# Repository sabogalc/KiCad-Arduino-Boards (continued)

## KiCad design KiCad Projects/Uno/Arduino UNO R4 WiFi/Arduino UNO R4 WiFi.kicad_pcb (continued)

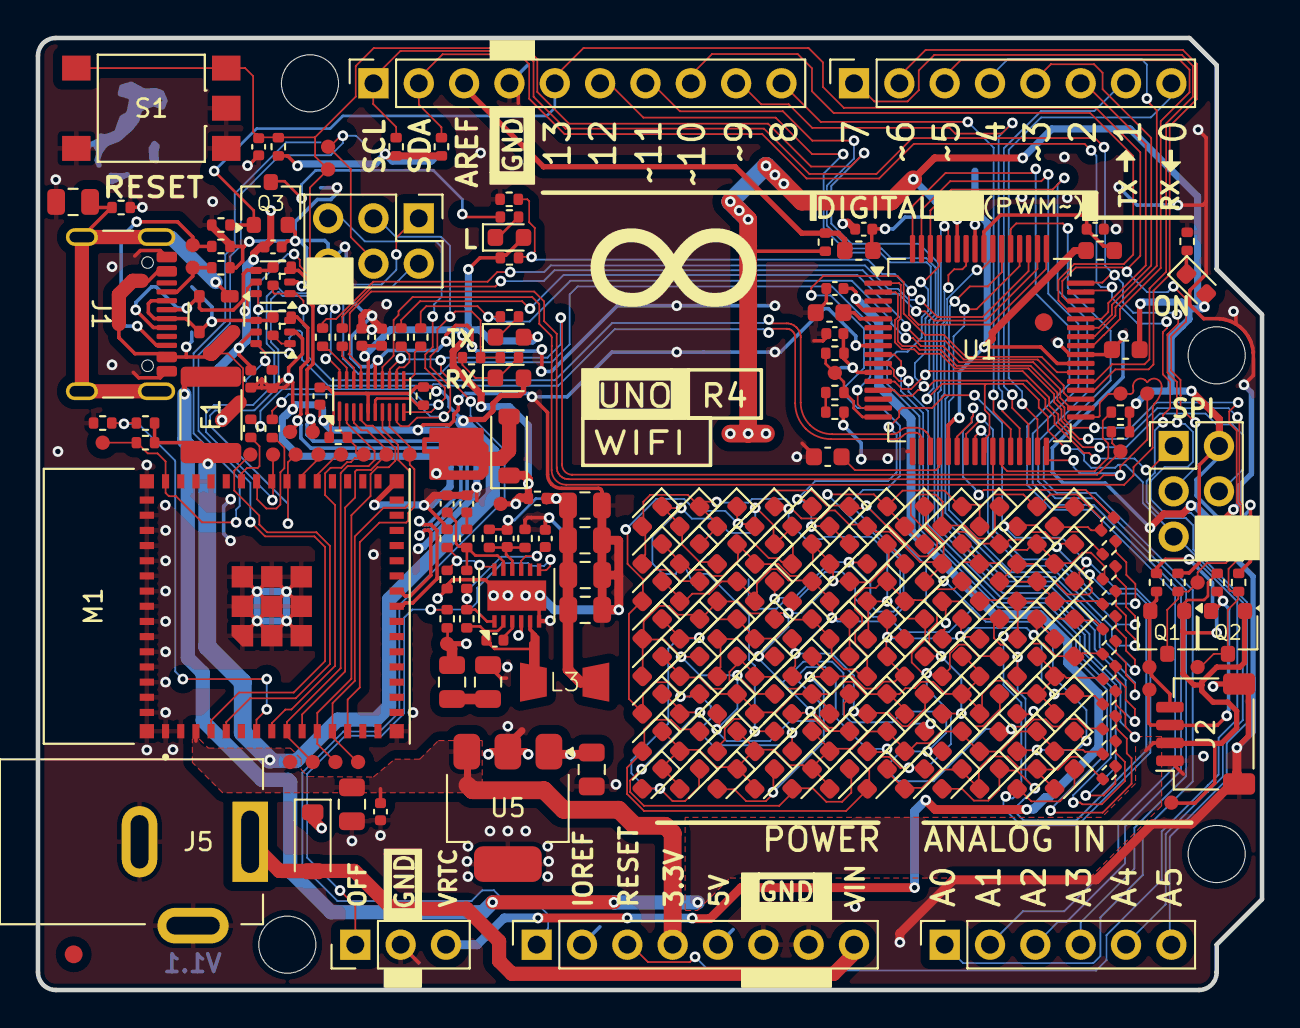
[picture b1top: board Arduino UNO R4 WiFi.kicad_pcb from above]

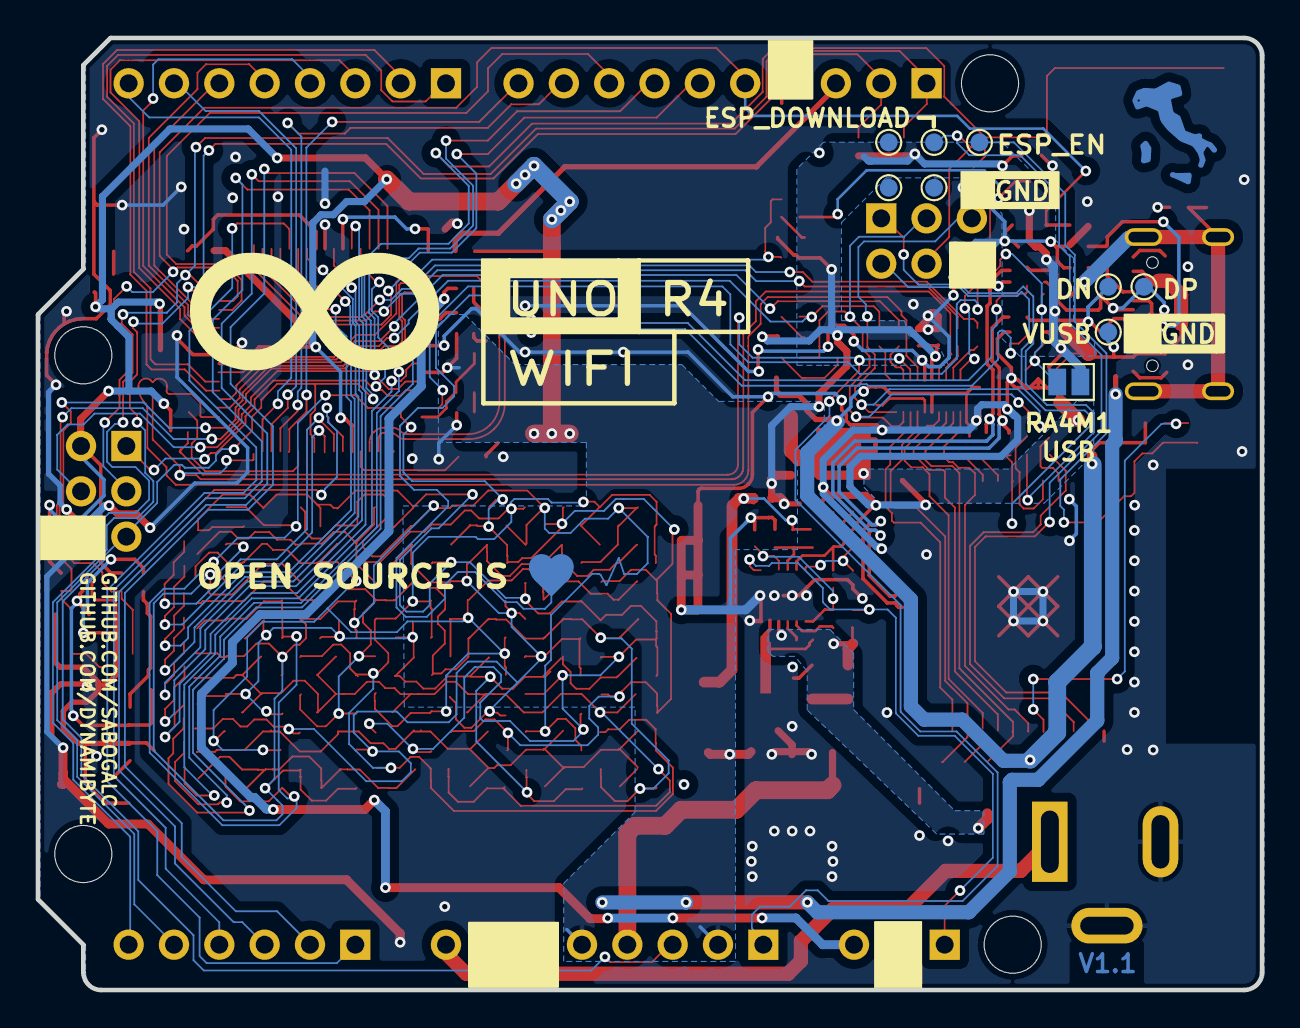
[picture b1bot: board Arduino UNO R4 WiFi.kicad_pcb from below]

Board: 2 copper layers, 68.6 x 53.3 mm, 262 parts (12 on the bottom side), 121 nets.

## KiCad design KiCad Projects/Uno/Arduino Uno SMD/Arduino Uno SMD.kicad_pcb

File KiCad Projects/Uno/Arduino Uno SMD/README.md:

# UNO R3 SMD
This board and its design process are essentially the same as the regular R3.

Below are the screenshots of this board from KiCad's 3D board viewer.

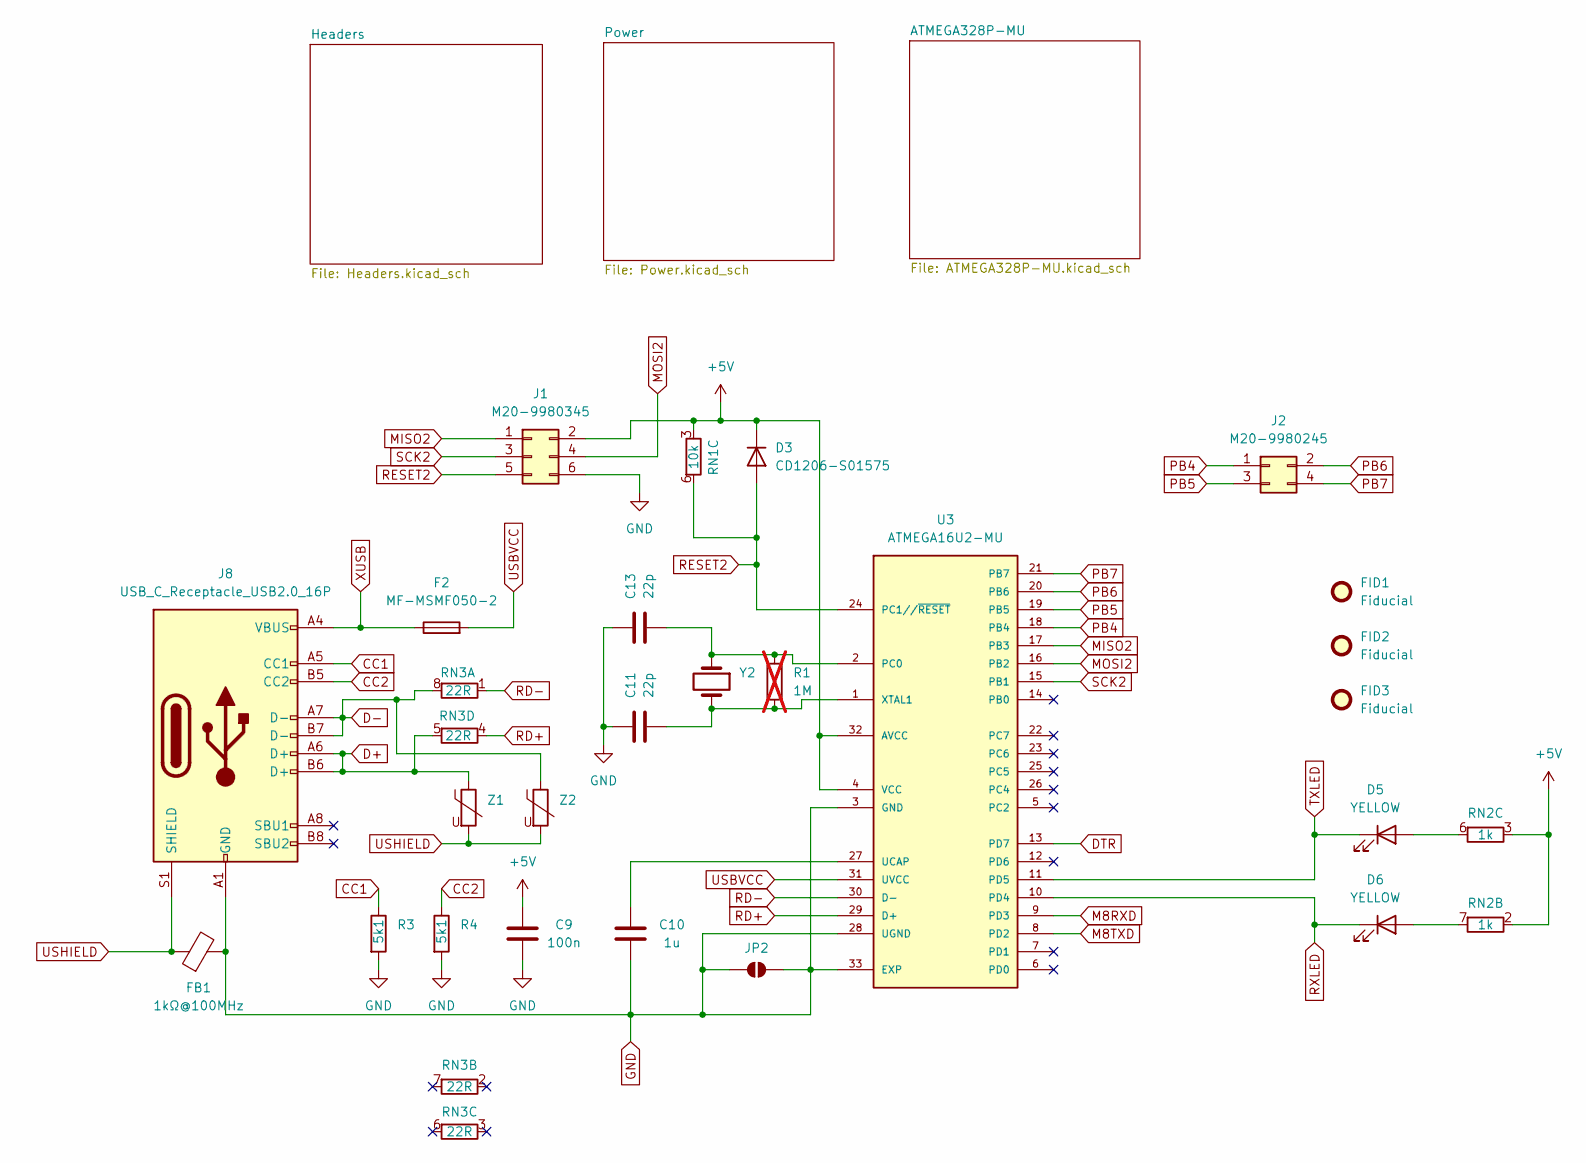
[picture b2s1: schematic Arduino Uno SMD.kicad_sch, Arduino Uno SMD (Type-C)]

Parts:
C9: 100n; C_0603_1608Metric
C10: 1u; C_0603_1608Metric
C11, C13: 22p; C_0603_1608Metric
D3: CD1206-S01575; D_1206_3216Metric
D5, D6: YELLOW; LED_0805_2012Metric
F2: MF-MSMF050-2; Fuse_1812_4532Metric_Pad1.30x3.40mm_HandSolder
FB1: 1kΩ@100MHz; L_0805_2012Metric
FID1, FID2, FID3: Fiducial; Fiducial_1mm_Mask2mm
J1: M20-9980345; PinHeader_2x03_P2.54mm_Vertical
J2: M20-9980245; CONN_M20-9980245_HRW
J8: USB_C_Receptacle_USB2.0_16P; USB_C_Receptacle_GCT_USB4105-xx-A_16P_TopMnt_Horizontal
JP2: SolderJumper_2_Open; SolderJumper-2_P1.3mm_Open_Pad1.0x1.5mm
R1: 1M; R_0603_1608Metric; not fitted
R3, R4: 5k1; R_0603_1608Metric
RN1: 10k; R_Array_Convex_4x0603
RN2: 1k; R_Array_Convex_4x0603
RN3: 22R; R_Array_Convex_4x0603
U3: ATMEGA16U2-MU; VQFN-32-1EP_5x5mm_P0.5mm_EP3.1x3.1mm
Y2: LFXTAL003240BULK; Crystal_HC49-4H_Vertical
Z1, Z2: 5pF@1MHz; R_0603_1608Metric

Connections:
+5V: C9.1, D3.1 (K), J1.2, RN1.3 (R3.1), RN2.2 (R2.1), RN2.3 (R3.1), U3.4 (VCC), U3.32 (AVCC); also elsewhere on the board
CC1: J8.A5 (CC1), R3.1
CC2: J8.B5 (CC2), R4.1
D+: J8.A6 (D+), J8.B6 (D+), RN3.5 (R4.2), Z1.1
D-: J8.A7 (D-), J8.B7 (D-), RN3.8 (R1.2), Z2.1
DTR: U3.13 (PD7); also elsewhere on the board
GND: C9.2, C10.1, C11.2, C13.2, FB1.2, J1.6, J8.A1 (GND), J8.A12 (GND), J8.B1 (GND), J8.B12 (GND), JP2.1 (A), JP2.2 (B), R3.2, R4.2, U3.3 (GND), U3.28 (UGND), U3.33 (EXP); also elsewhere on the board
M8RXD: U3.9 (PD3); also elsewhere on the board
M8TXD: U3.8 (PD2); also elsewhere on the board
MISO2: J1.1, U3.17 (PB3)
MOSI2: J1.4, U3.16 (PB2)
unnamed: D5.2 (A), RN2.6 (R3.2)
unnamed: D6.2 (A), RN2.7 (R2.2)
unnamed: C13.1, R1.1, U3.2 (PC0), Y2.1
unnamed: C10.2, U3.27 (UCAP)
unnamed: C11.1, R1.2, U3.1 (XTAL1), Y2.2
PB4: J2.1, U3.18 (PB4)
PB5: J2.3, U3.19 (PB5)
PB6: J2.2, U3.20 (PB6)
PB7: J2.4, U3.21 (PB7)
RD+: RN3.4 (R4.1), U3.29 (D+)
RD-: RN3.1 (R1.1), U3.30 (D-)
RESET2: D3.2 (A), J1.5, RN1.6 (R3.2), U3.24 (PC1//~RESET)
RXLED: D6.1 (K), U3.10 (PD4)
SCK2: J1.3, U3.15 (PB1)
TXLED: D5.1 (K), U3.11 (PD5)
USBVCC: F2.2, U3.31 (UVCC); also elsewhere on the board
USHIELD: FB1.1, J8.S1 (SHIELD), Z1.2, Z2.2
XUSB: F2.1, J8.A4 (VBUS), J8.A9 (VBUS), J8.B4 (VBUS), J8.B9 (VBUS)

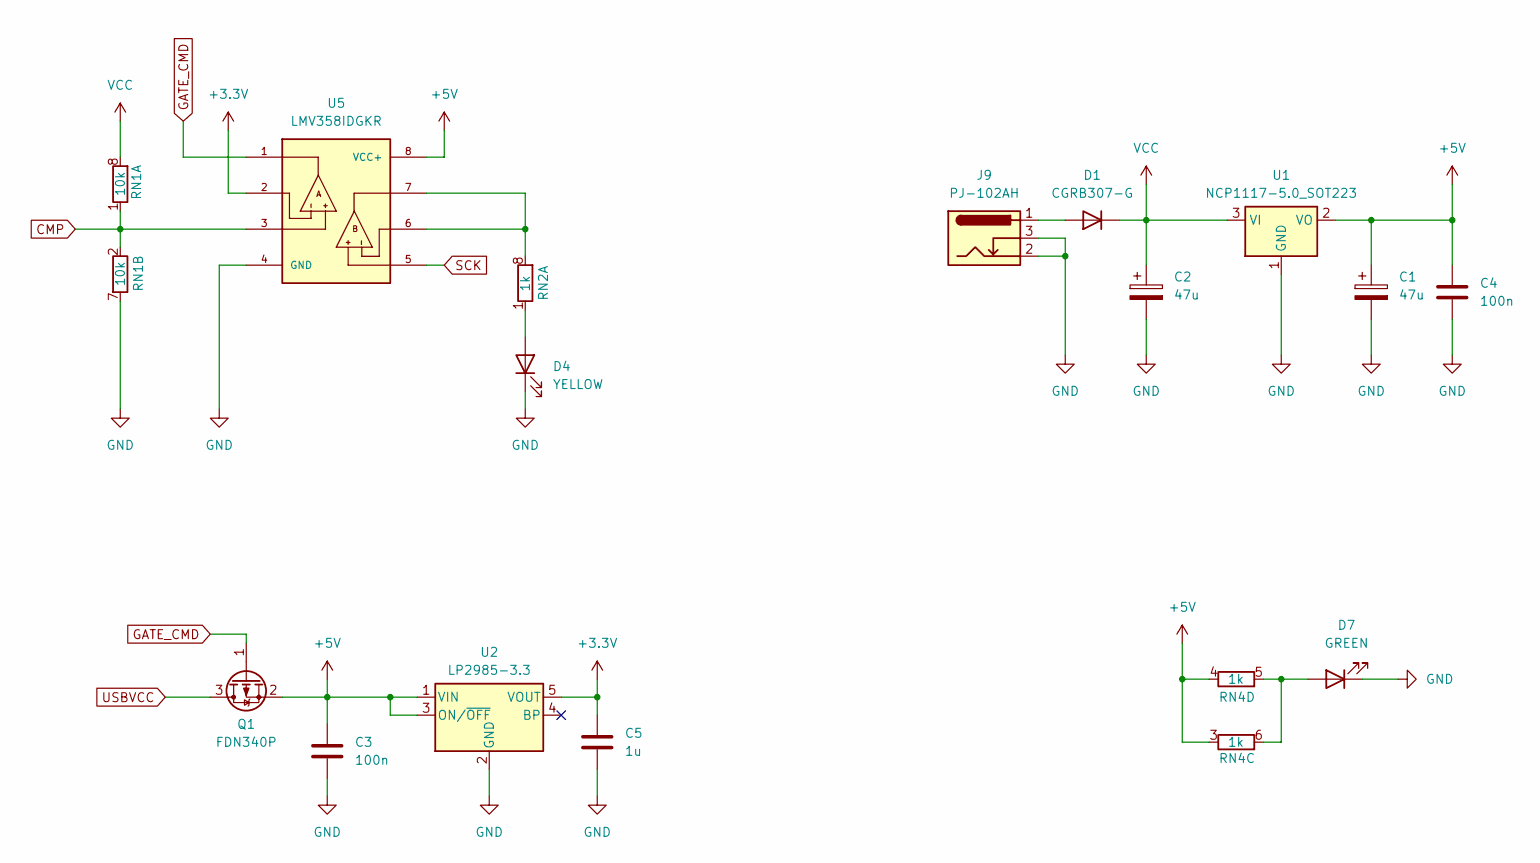
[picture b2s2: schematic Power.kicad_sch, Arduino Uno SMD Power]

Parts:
C1, C2: 47u; CAP_EEHZA1E470P
C3, C4: 100n; C_0603_1608Metric
C5: 1u; C_0603_1608Metric
D1: CGRB307-G; D_SMB
D4: YELLOW; LED_0805_2012Metric
D7: GREEN; LED_0805_2012Metric
J9: PJ-102AH; BarrelJack_Kycon_KLDX-0202-xC_Horizontal
Q1: FDN340P; SC-59
RN1: 10k; R_Array_Convex_4x0603
RN2, RN4: 1k; R_Array_Convex_4x0603
U1: NCP1117-5.0_SOT223; SOT-223-3_TabPin2
U2: LP2985-3.3; SOT-23-5
U5: LMV358IDGKR; MSOP-8_3x3mm_P0.65mm; PARTREV X

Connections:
+3.3V: C5.2, U2.5 (VOUT), U5.2; also elsewhere on the board
+5V: C1.1, C3.2, C4.1, Q1.2 (S), RN4.3 (R3.1), RN4.4 (R4.1), U1.2 (VO), U2.1 (VIN), U2.3 (ON/~OFF), U5.8 (VCC+); also elsewhere on the board
CMP: RN1.1 (R1.1), RN1.2 (R2.1), U5.3
GATE_CMD: Q1.1 (G), U5.1
GND: C1.2, C2.2, C3.1, C4.2, C5.1, D4.1 (K), D7.1 (K), J9.2, J9.3, RN1.7 (R2.2), U1.1 (GND), U2.2 (GND), U5.4 (GND); also elsewhere on the board
unnamed: D1.2 (A), J9.1
unnamed: D4.2 (A), RN2.1 (R1.1)
unnamed: D7.2 (A), RN4.5 (R4.2), RN4.6 (R3.2)
unnamed: RN2.8 (R1.2), U5.6, U5.7
SCK: U5.5; also elsewhere on the board
USBVCC: Q1.3 (D); also elsewhere on the board
VCC: C2.1, D1.1 (K), RN1.8 (R1.2), U1.3 (VI); also elsewhere on the board

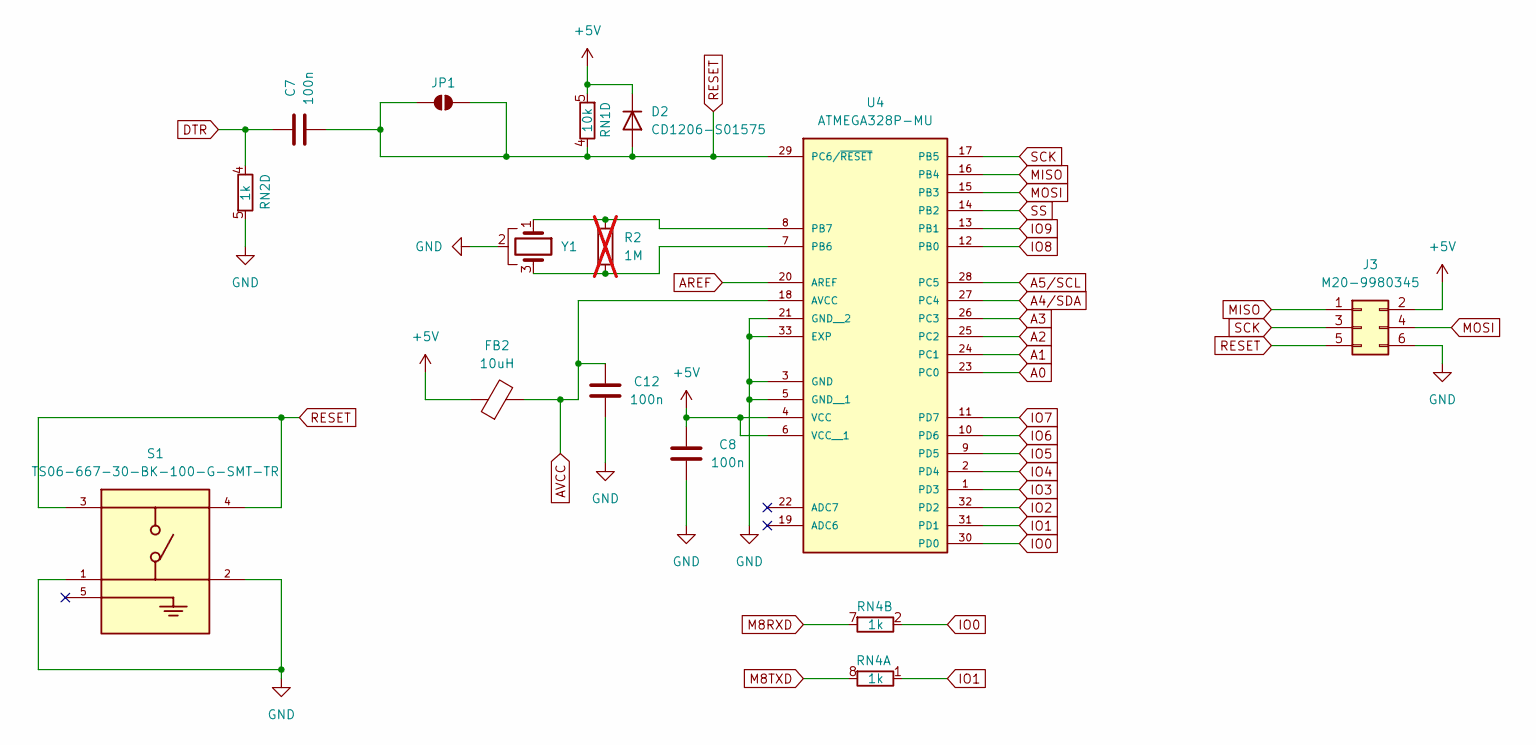
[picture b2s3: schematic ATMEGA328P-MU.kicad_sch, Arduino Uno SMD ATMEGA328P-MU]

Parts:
C7, C8, C12: 100n; C_0603_1608Metric
D2: CD1206-S01575; D_1206_3216Metric
FB2: 10uH; L_0805_2012Metric
J3: M20-9980345; PinHeader_2x03_P2.54mm_Vertical
JP1: SolderJumper_2_Open; SolderJumper-2_P1.3mm_Open_Pad1.0x1.5mm
R2: 1M; R_0603_1608Metric; not fitted
RN1: 10k; R_Array_Convex_4x0603
RN2, RN4: 1k; R_Array_Convex_4x0603
S1: TS06-667-30-BK-100-G-SMT-TR; SW_TS06-667-30-BK-100-G-SMT-TR; PARTREV 1.0
U4: ATMEGA328P-MU; VQFN-32-1EP_5x5mm_P0.5mm_EP3.1x3.1mm
Y1: CSTNE16M0V530000R0; Resonator_SMD_Murata_CSTxExxV-3Pin_3.0x1.1mm

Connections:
+5V: C8.2, D2.1 (K), FB2.1, J3.2, RN1.5 (R4.2), U4.4 (VCC), U4.6 (VCC__1); also elsewhere on the board
A0: U4.23 (PC0); also elsewhere on the board
A1: U4.24 (PC1); also elsewhere on the board
A2: U4.25 (PC2); also elsewhere on the board
A3: U4.26 (PC3); also elsewhere on the board
A4/SDA: U4.27 (PC4); also elsewhere on the board
A5/SCL: U4.28 (PC5); also elsewhere on the board
AREF: U4.20 (AREF); also elsewhere on the board
AVCC: C12.1, FB2.2, U4.18 (AVCC)
DTR: C7.1, RN2.4 (R4.1); also elsewhere on the board
GND: C8.1, C12.2, J3.6, RN2.5 (R4.2), S1.1, S1.2, U4.3 (GND), U4.5 (GND__1), U4.21 (GND__2), U4.33 (EXP), Y1.2; also elsewhere on the board
IO0: RN4.2 (R2.1), U4.30 (PD0); also elsewhere on the board
IO1: RN4.1 (R1.1), U4.31 (PD1); also elsewhere on the board
IO2: U4.32 (PD2); also elsewhere on the board
IO3: U4.1 (PD3); also elsewhere on the board
IO4: U4.2 (PD4); also elsewhere on the board
IO5: U4.9 (PD5); also elsewhere on the board
IO6: U4.10 (PD6); also elsewhere on the board
IO7: U4.11 (PD7); also elsewhere on the board
IO8: U4.12 (PB0); also elsewhere on the board
IO9: U4.13 (PB1); also elsewhere on the board
M8RXD: RN4.7 (R2.2); also elsewhere on the board
M8TXD: RN4.8 (R1.2); also elsewhere on the board
MISO: J3.1, U4.16 (PB4); also elsewhere on the board
MOSI: J3.4, U4.15 (PB3); also elsewhere on the board
unnamed: R2.2, U4.7 (PB6), Y1.3
unnamed: R2.1, U4.8 (PB7), Y1.1
RESET: C7.2, D2.2 (A), J3.5, JP1.1 (A), JP1.2 (B), RN1.4 (R4.1), S1.3, S1.4, U4.29 (PC6/~RESET); also elsewhere on the board
SCK: J3.3, U4.17 (PB5); also elsewhere on the board
SS: U4.14 (PB2); also elsewhere on the board

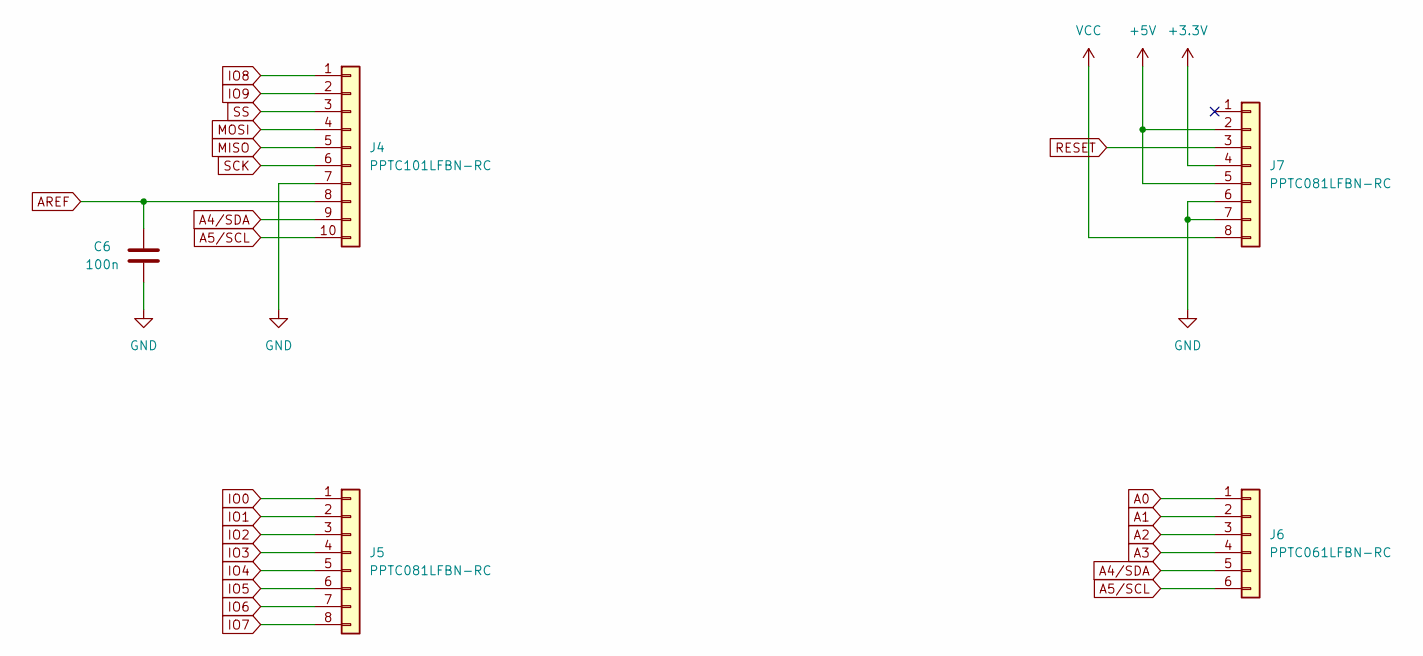
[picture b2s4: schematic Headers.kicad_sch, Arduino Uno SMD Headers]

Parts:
C6: 100n; C_0603_1608Metric
J4: PPTC101LFBN-RC; PinSocket_1x10_P2.54mm_Vertical
J5, J7: PPTC081LFBN-RC; PinSocket_1x08_P2.54mm_Vertical
J6: PPTC061LFBN-RC; PinSocket_1x06_P2.54mm_Vertical

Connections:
+3.3V: J7.4; also elsewhere on the board
+5V: J7.2, J7.5; also elsewhere on the board
A0: J6.1; also elsewhere on the board
A1: J6.2; also elsewhere on the board
A2: J6.3; also elsewhere on the board
A3: J6.4; also elsewhere on the board
A4/SDA: J4.9, J6.5; also elsewhere on the board
A5/SCL: J4.10, J6.6; also elsewhere on the board
AREF: C6.1, J4.8; also elsewhere on the board
GND: C6.2, J4.7, J7.6, J7.7; also elsewhere on the board
IO0: J5.1; also elsewhere on the board
IO1: J5.2; also elsewhere on the board
IO2: J5.3; also elsewhere on the board
IO3: J5.4; also elsewhere on the board
IO4: J5.5; also elsewhere on the board
IO5: J5.6; also elsewhere on the board
IO6: J5.7; also elsewhere on the board
IO7: J5.8; also elsewhere on the board
IO8: J4.1; also elsewhere on the board
IO9: J4.2; also elsewhere on the board
MISO: J4.5; also elsewhere on the board
MOSI: J4.4; also elsewhere on the board
RESET: J7.3; also elsewhere on the board
SCK: J4.6; also elsewhere on the board
SS: J4.3; also elsewhere on the board
VCC: J7.8; also elsewhere on the board

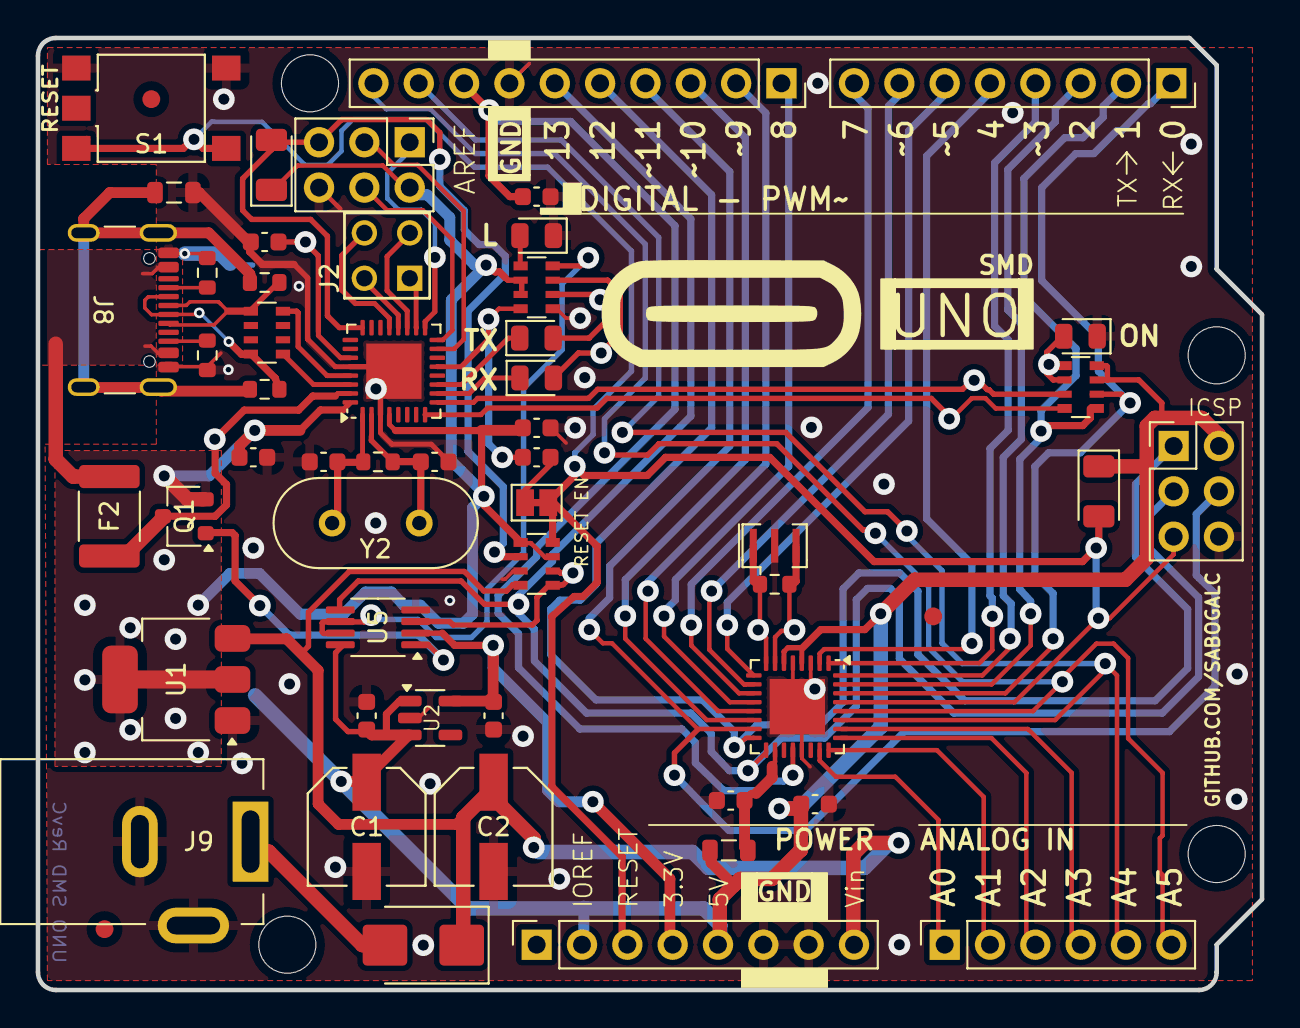
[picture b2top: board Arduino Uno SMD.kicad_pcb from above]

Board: 2 copper layers, 68.6 x 53.3 mm, 56 parts (1 on the bottom side), 62 nets.

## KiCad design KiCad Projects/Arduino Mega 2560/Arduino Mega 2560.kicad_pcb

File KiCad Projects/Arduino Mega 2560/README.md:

# Mega 2560
I was expecting this to be the most difficult board to make, but it really wasn't all that bad. It did take the longest, but I broke up the design into small sessions across multiple days.

I don't currently have any projects that require the whopping 54 GPIO pins that this board offers, but I saw that it was commonly used in the robotics and 3D printing spaces, and I've also seen it used to read EEPROM data on Ben Eater's YouTube channel.

Below are the screenshots of this board from KiCad's 3D board viewer.

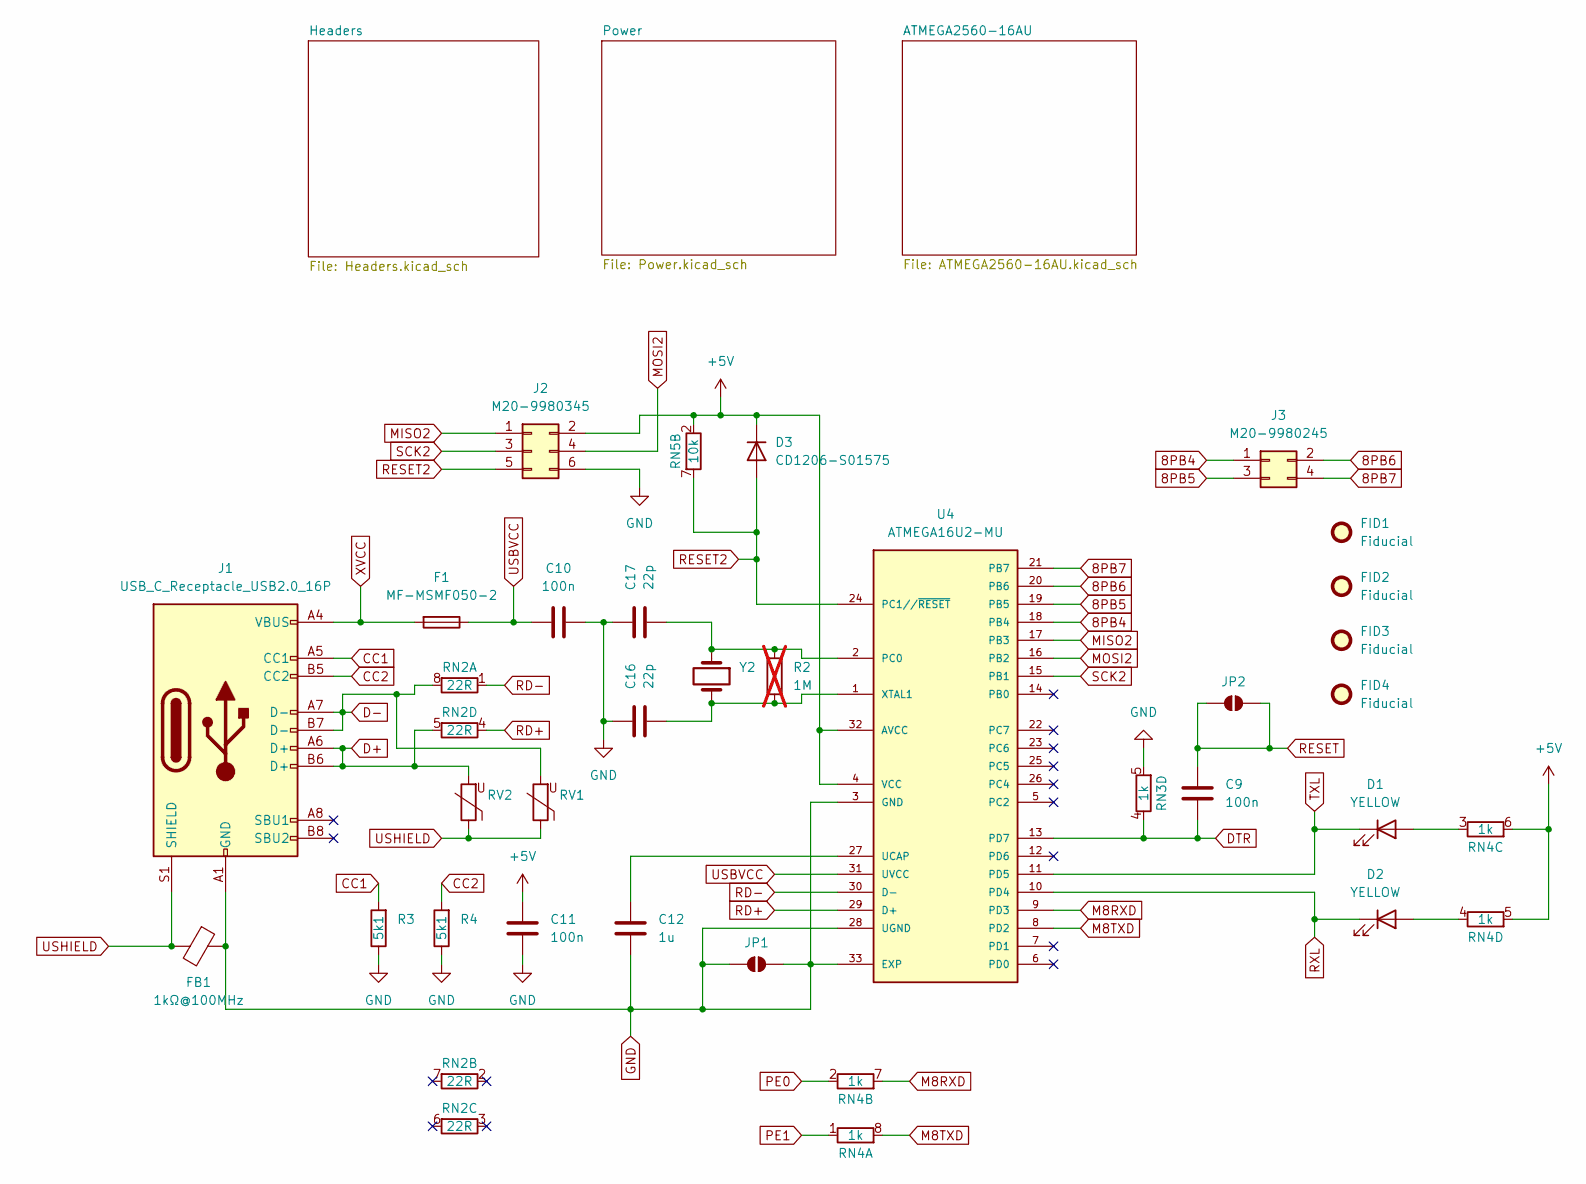
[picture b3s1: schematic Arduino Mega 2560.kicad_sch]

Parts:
C9, C10, C11: 100n; C_0603_1608Metric
C12: 1u; C_0603_1608Metric
C16, C17: 22p; C_0603_1608Metric
D1, D2: YELLOW; LED_0805_2012Metric
D3: CD1206-S01575; D_1206_3216Metric
F1: MF-MSMF050-2; Fuse_1812_4532Metric_Pad1.30x3.40mm_HandSolder
FB1: 1kΩ@100MHz; L_0805_2012Metric
FID1, FID2, FID3, FID4: Fiducial; Fiducial_1mm_Mask3mm
J1: USB_C_Receptacle_USB2.0_16P; USB_C_Receptacle_GCT_USB4105-xx-A_16P_TopMnt_Horizontal
J2: M20-9980345; PinHeader_2x03_P2.54mm_Vertical
J3: M20-9980245; CONN_M20-9980245_HRW
JP1, JP2: SolderJumper_2_Open; SolderJumper-2_P1.3mm_Open_Pad1.0x1.5mm
R2: 1M; R_0603_1608Metric; not fitted
R3, R4: 5k1; R_0603_1608Metric
RN2: 22R; R_Array_Convex_4x0612
RN3, RN4: 1k; R_Array_Convex_4x0612
RN5: 10k; R_Array_Convex_4x0612
RV1, RV2: 5pF@1MHz; R_0603_1608Metric
U4: ATMEGA16U2-MU; VQFN-32-1EP_5x5mm_P0.5mm_EP3.1x3.1mm
Y2: LFXTAL003240BULK; Crystal_HC49-4H_Vertical

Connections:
8PB4: J3.1, U4.18 (PB4)
8PB5: J3.3, U4.19 (PB5)
8PB6: J3.2, U4.20 (PB6)
8PB7: J3.4, U4.21 (PB7)
+5V: C11.1, D3.1 (K), J2.2, RN4.5 (R4.2), RN4.6 (R3.2), RN5.2 (R2.1), U4.4 (VCC), U4.32 (AVCC); also elsewhere on the board
CC1: J1.A5 (CC1), R3.2
CC2: J1.B5 (CC2), R4.2
D+: J1.A6 (D+), J1.B6 (D+), RN2.5 (R4.2), RV2.2
D-: J1.A7 (D-), J1.B7 (D-), RN2.8 (R1.2), RV1.2
DTR: C9.1, RN3.4 (R4.1), U4.13 (PD7)
GND: C10.2, C11.2, C12.2, C16.2, C17.2, FB1.1, J1.A1 (GND), J1.A12 (GND), J1.B1 (GND), J1.B12 (GND), J2.6, JP1.1 (A), JP1.2 (B), R3.1, R4.1, RN3.5 (R4.2), U4.3 (GND), U4.28 (UGND), U4.33 (EXP); also elsewhere on the board
M8RXD: RN4.7 (R2.2), U4.9 (PD3)
M8TXD: RN4.8 (R1.2), U4.8 (PD2)
MISO2: J2.1, U4.17 (PB3)
MOSI2: J2.4, U4.16 (PB2)
unnamed: D1.2 (A), RN4.3 (R3.1)
unnamed: D2.2 (A), RN4.4 (R4.1)
unnamed: C17.1, R2.2, U4.2 (PC0), Y2.1
unnamed: C12.1, U4.27 (UCAP)
unnamed: C16.1, R2.1, U4.1 (XTAL1), Y2.2
PE0: RN4.2 (R2.1); also elsewhere on the board
PE1: RN4.1 (R1.1); also elsewhere on the board
RD+: RN2.4 (R4.1), U4.29 (D+)
RD-: RN2.1 (R1.1), U4.30 (D-)
RESET: C9.2, JP2.1 (A), JP2.2 (B); also elsewhere on the board
RESET2: D3.2 (A), J2.5, RN5.7 (R2.2), U4.24 (PC1//~RESET)
RXL: D2.1 (K), U4.10 (PD4)
SCK2: J2.3, U4.15 (PB1)
TXL: D1.1 (K), U4.11 (PD5)
USBVCC: C10.1, F1.1, U4.31 (UVCC); also elsewhere on the board
USHIELD: FB1.2, J1.S1 (SHIELD), RV1.1, RV2.1
XVCC: F1.2, J1.A4 (VBUS), J1.A9 (VBUS), J1.B4 (VBUS), J1.B9 (VBUS)

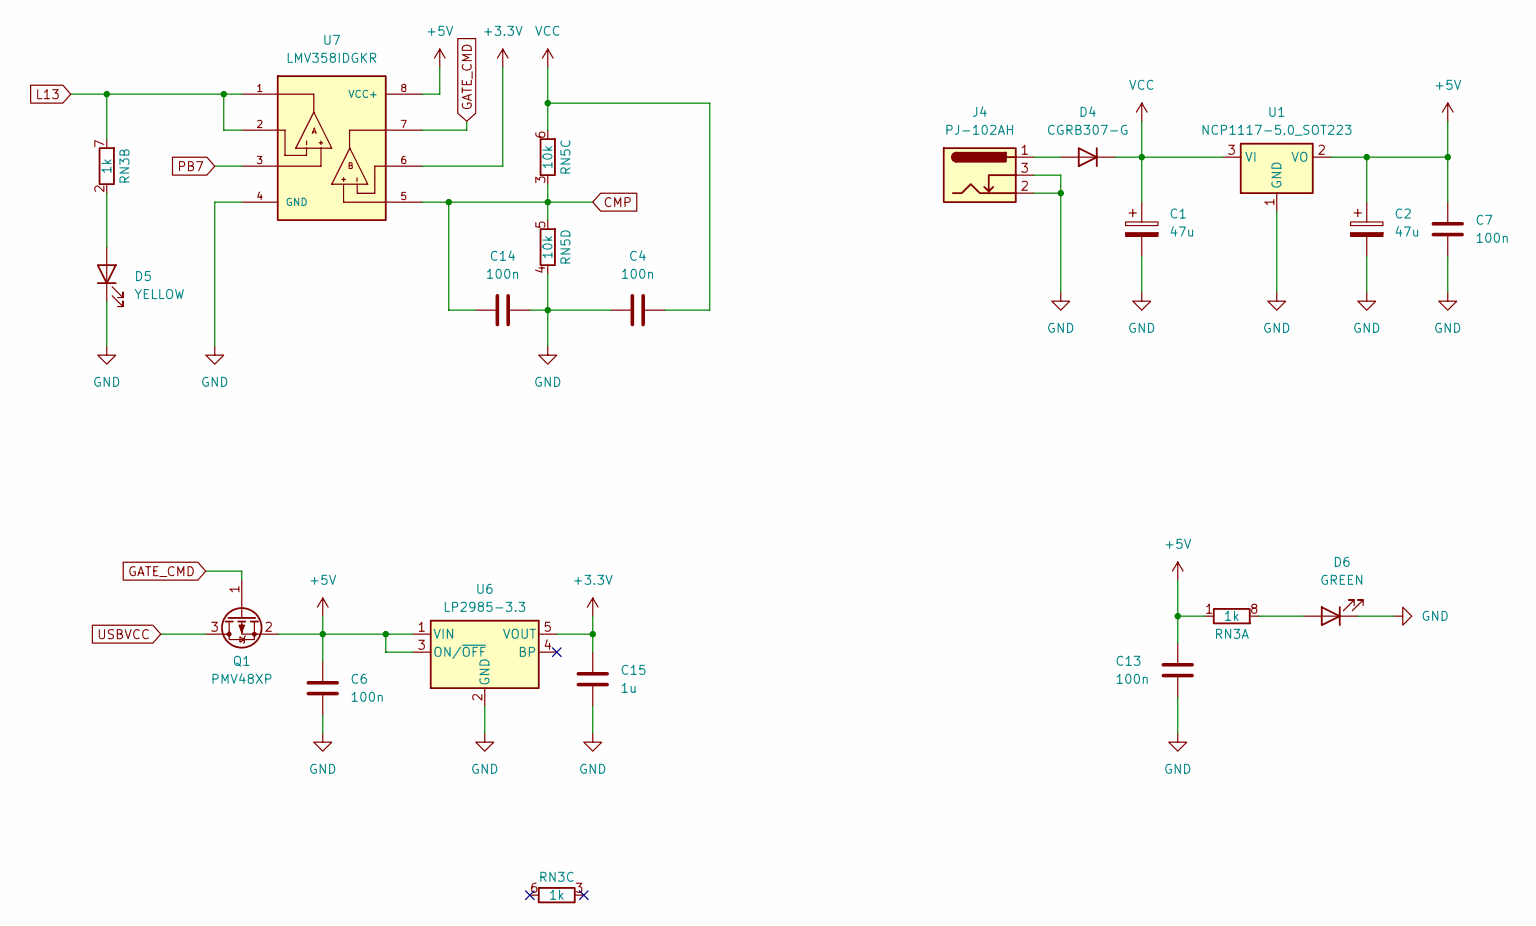
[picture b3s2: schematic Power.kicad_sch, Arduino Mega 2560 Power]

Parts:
C1, C2: 47u; CAP_EEHZA1E470P
C4, C6, C7, C13, C14: 100n; C_0603_1608Metric
C15: 1u; C_0603_1608Metric
D4: CGRB307-G; D_SMB
D5: YELLOW; LED_0805_2012Metric
D6: GREEN; LED_0805_2012Metric
J4: PJ-102AH; BarrelJack_Kycon_KLDX-0202-xC_Horizontal
Q1: PMV48XP; SC-59
RN3: 1k; R_Array_Convex_4x0612
RN5: 10k; R_Array_Convex_4x0612
U1: NCP1117-5.0_SOT223; SOT-223-3_TabPin2
U6: LP2985-3.3; SOT-23-5
U7: LMV358IDGKR; MSOP-8_3x3mm_P0.65mm; PARTREV X

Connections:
+3.3V: C15.2, U6.5 (VOUT), U7.6; also elsewhere on the board
+5V: C2.1, C6.1, C7.1, C13.2, Q1.2 (S), RN3.1 (R1.1), U1.2 (VO), U6.1 (VIN), U6.3 (ON/~OFF), U7.8 (VCC+); also elsewhere on the board
CMP: C14.2, RN5.3 (R3.1), RN5.5 (R4.2), U7.5
GATE_CMD: Q1.1 (G), U7.7
GND: C1.2, C2.2, C4.2, C6.2, C7.2, C13.1, C14.1, C15.1, D5.1 (K), D6.1 (K), J4.2, J4.3, RN5.4 (R4.1), U1.1 (GND), U6.2 (GND), U7.4 (GND); also elsewhere on the board
L13: RN3.7 (R2.2), U7.1, U7.2
unnamed: D4.2 (A), J4.1
unnamed: D5.2 (A), RN3.2 (R2.1)
unnamed: D6.2 (A), RN3.8 (R1.2)
PB7: U7.3; also elsewhere on the board
USBVCC: Q1.3 (D); also elsewhere on the board
VCC: C1.1, C4.1, D4.1 (K), RN5.6 (R3.2), U1.3 (VI); also elsewhere on the board
